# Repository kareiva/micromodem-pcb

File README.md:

# LY2EN-made MicroModem Arduino Nano shield

PCB and schematics for a very basic [MicroModem](https://unsigned.io/micromodem/) shield for Arduino Nano to use with Baofeng radios.

## Disclaimer

This is experimental work. The authors do not hold any responsibility for any damage to your electronics components, wiring or other property when using this prototype. Use at your own risk.

## How to use

1. Upload the [MicroAPRS 3v KISS firmware](https://github.com/markqvist/MicroAPRS/raw/master/precompiled/microaprs-3v-kiss-latest.hex) to the Arduino Nano:

    avrdude -p m328p -c arduino -P /dev/ttyUSB0 -b 115200 -U flash:w:microaprs-3v-kiss-latest.hex

2. Plug the Arduino Nano into your Android phone's USB host

3. Launch [APRSDroid](https://aprsdroid.org/) 

    3.1 Select TNC (KISS) mode over USB. 
    
    3.2 Keep the baud rate at 9600.
    
4. Set the 3296W trimmer to something around 47kOhm. Your resistance might vary here. Once you're confident, you can replace it with a simple 47k resistor.

Verified working with both the MicroAPRS KISS and MicroAPRS SimpleSerial firmware for 3V.

## Cables

If you're not using a [Bluetooth SPP-C module](https://www.aliexpress.com/item/32998624269.html), a USB-C male to USB-A female adapter is required for recent Android smartphones.

Connect to Baofeng radio over [this cable](https://a.aliexpress.com/_mNhKQOm).

### Pinout
The Baofeng cable has two TRS (Tip, Ring, Sleeve) connectors.
#### 3.5mm
* Sleeve - PTT
* Ring - OUT
#### 2.5mm
* Sleeve - GND
* Tip - IN

## Features / Changelog

### Version 0.4
* Added pin hole connector for SPP-C Bluetooth module

### Version 0.3 (verified)
* Upgraded to KiCad version 6
* Fixed edge cut layer (Edge.Cuts)
* Re-rendered PCB 3D visual with ray tracing
* Added JLCPCB compatible BOM and CPL files
* Ordered test batch from JLCPCB :)
* **Verified working!**

### Version 0.2
* Traces widened from 0.25 to 0.5mm
* Added GND area fill on the back side
* Signature added :)

### Version 0.1
* Only the ANALOG_IN, ANALOG_OUT and PTT are exposed.
* PTT wiring has been done as per Baofeng schematics.
* Tested with 3.3V MicroModem's [SimpleSerial](https://github.com/markqvist/MicroAPRS/raw/master/precompiled/microaprs-3v-ss-latest.hex) and [KISS](https://github.com/markqvist/MicroModemGP/raw/master/precompiled/MicroModemGP-3v-kiss.hex) firmware.
* Assuming that RST, XTAL, SPI pins, the CH340 and the rest of stuff is on the Nano already
* Wiring is done for 3.3V, so make sure to use the 3.3V MicroModem hex (see above).

## TODO

* Replace Q1 with SMT version

## Authors

PCB made by Simonas Kareiva LY2EN (<ly2en@qrz.lt>) using KiCad and by looking at the [original schematics](https://unsigned.io/wp-content/uploads/2014/12/Schematic-1.pdf).

Inspiration by [Vilius LY3FF](https://github.com/vilisas/).

MicroModem originally by https://github.com/markqvist

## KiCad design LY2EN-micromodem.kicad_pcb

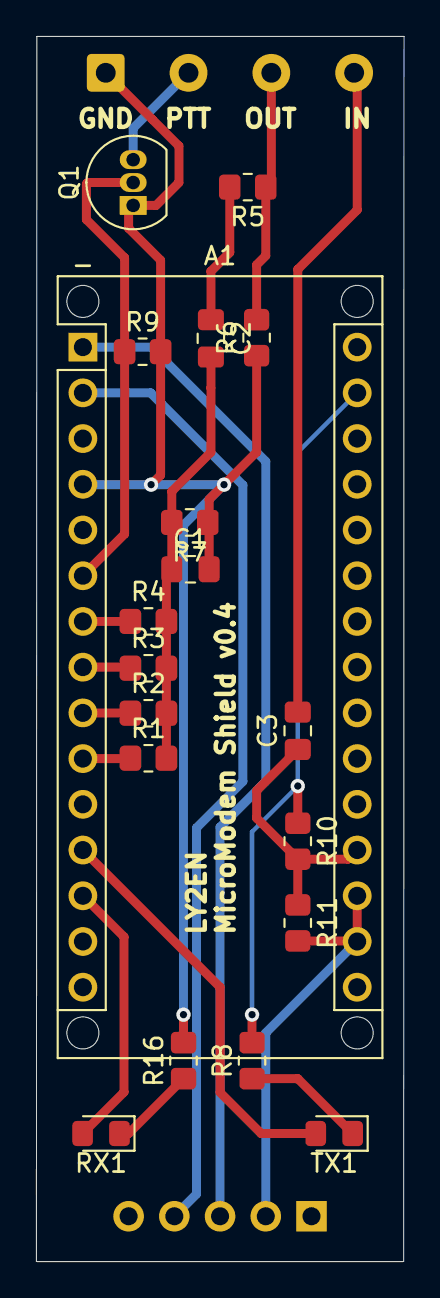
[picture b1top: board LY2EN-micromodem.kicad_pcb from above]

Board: 2 copper layers, 20.4 x 68.1 mm, 21 parts (1 on the bottom side), 19 nets.

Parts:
A1: Arduino_Nano_Every; Arduino_Nano_WithMountingHoles
C1: 100nF; C_0805_2012Metric_Pad1.18x1.45mm_HandSolder
C2: 4.7uF; C_0805_2012Metric_Pad1.18x1.45mm_HandSolder
C3: 1uF; C_0805_2012Metric_Pad1.18x1.45mm_HandSolder
Conn_01x5: BT_MOD; PinSocket_1x05_P2.54mm_Vertical
Q1: 2N7000; TO-92_Inline
R1, R6, R16: 1k; R_0805_2012Metric_Pad1.20x1.40mm_HandSolder
R2: 2k2; R_0805_2012Metric_Pad1.20x1.40mm_HandSolder
R3: 3k9; R_0805_2012Metric_Pad1.20x1.40mm_HandSolder
R4: 8k2; R_0805_2012Metric_Pad1.20x1.40mm_HandSolder
R5: 47k; R_0805_2012Metric_Pad1.20x1.40mm_HandSolder
R7, R8: 270; R_0805_2012Metric_Pad1.20x1.40mm_HandSolder
R9: 10k; R_0805_2012Metric_Pad1.20x1.40mm_HandSolder
R10, R11: 100k; R_0805_2012Metric_Pad1.20x1.40mm_HandSolder
RX1: LED; LED_0805_2012Metric_Pad1.15x1.40mm_HandSolder
TX1: LED; LED_0805_2012Metric_Pad1.15x1.40mm_HandSolder
_: SolderWire; SolderWire-0.5sqmm_1x04_P4.6mm_D0.9mm_OD2.1mm

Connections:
ANALOG_IN: C3.2, _.4
ANALOG_OUT: R5.1, R6.2, _.3
GND: A1.4 (GND), A1.29 (GND), C1.2, Conn_01x5.1, Conn_01x5.5, Q1.1 (S), R6.1, R7.1, R8.2, R9.2, R10.1, R16.2, _.1
unnamed: A1.1 (TX1), Conn_01x5.3
unnamed: A1.2 (RX1), Conn_01x5.4
unnamed: A1.6 (D3), Q1.2 (G), R9.1
unnamed: A1.7 (D4), R4.1
unnamed: A1.8 (D5), R3.1
unnamed: A1.9 (D6), R2.1
unnamed: A1.10 (D7), R1.1
unnamed: A1.12 (D9), TX1.2 (A)
unnamed: A1.13 (D10), RX1.2 (A)
unnamed: A1.17 (3V3), A1.18 (AREF), Conn_01x5.2, R11.2
unnamed: A1.19 (A0), C3.1, R10.2, R11.1
unnamed: C1.1, C2.2, R1.2, R2.2, R3.2, R4.2, R7.2
unnamed: C2.1, R5.2
unnamed: R8.1, TX1.1 (K)
unnamed: R16.1, RX1.1 (K)
PTT_V+: Q1.3 (D), _.2

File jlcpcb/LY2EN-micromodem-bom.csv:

Comment,Designator,Package,JLCPCB Part #（optional）
100nF,C1,C_0805_2012Metric_Pad1.18x1.45mm_HandSolder,
1uF,C3,C_0805_2012Metric_Pad1.18x1.45mm_HandSolder,
100k,R5,Potentiometer_Bourns_3296W_Vertical,C132869
270,"R7,R8",R_0805_2012Metric_Pad1.20x1.40mm_HandSolder,
100k,"R11,R10",R_0805_2012Metric_Pad1.20x1.40mm_HandSolder,
1k,"R16,R6,R1",R_0805_2012Metric_Pad1.20x1.40mm_HandSolder,
LED,TX1,LED_0805_2012Metric_Pad1.15x1.40mm_HandSolder,C84256
LED,RX1,LED_0805_2012Metric_Pad1.15x1.40mm_HandSolder,C2296
4.7uF,C2,C_0805_2012Metric_Pad1.18x1.45mm_HandSolder,
Arduino_Nano_Every,A1,Arduino_Nano_WithMountingHoles,
10k,R9,R_0805_2012Metric_Pad1.20x1.40mm_HandSolder,
2k2,R2,R_0805_2012Metric_Pad1.20x1.40mm_HandSolder,
3k9,R3,R_0805_2012Metric_Pad1.20x1.40mm_HandSolder,
8k2,R4,R_0805_2012Metric_Pad1.20x1.40mm_HandSolder,
2N7000,Q1,TO-92_Inline,C9114

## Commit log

2021-04-29 Initial commit + README
2021-04-29 Shrink SMD components down from 1812 to 0805
2021-04-29 PCB version 0.1
2021-04-30 Improved PCB layout: 0.5mm tracks and GND zone
2021-07-02 Add exported schematics in PNG format
2022-05-09 Upgrade to KiCad version 6
2022-05-09 Bump to version 0.3
2022-05-31 Verified working v0.3
2022-06-09 Update README with proper firmware references
2022-06-13 Add Bluetooth SPP-C serial passthrough support
2022-07-18 Replace potentiometer with static 47k resistor
2022-07-18 Fix bottom zone fill
2024-07-17 Update LY2EN-micromodem-bom.csv
    Removed R9 from line 4
2024-07-18 Removed R9 from line 4
    Removed R9 from line 4
2024-08-08 Update README.md
    More information about the Baofeng cable pinout
2024-08-09 Update README.md (#5)
    More information about the Baofeng cable pinout
